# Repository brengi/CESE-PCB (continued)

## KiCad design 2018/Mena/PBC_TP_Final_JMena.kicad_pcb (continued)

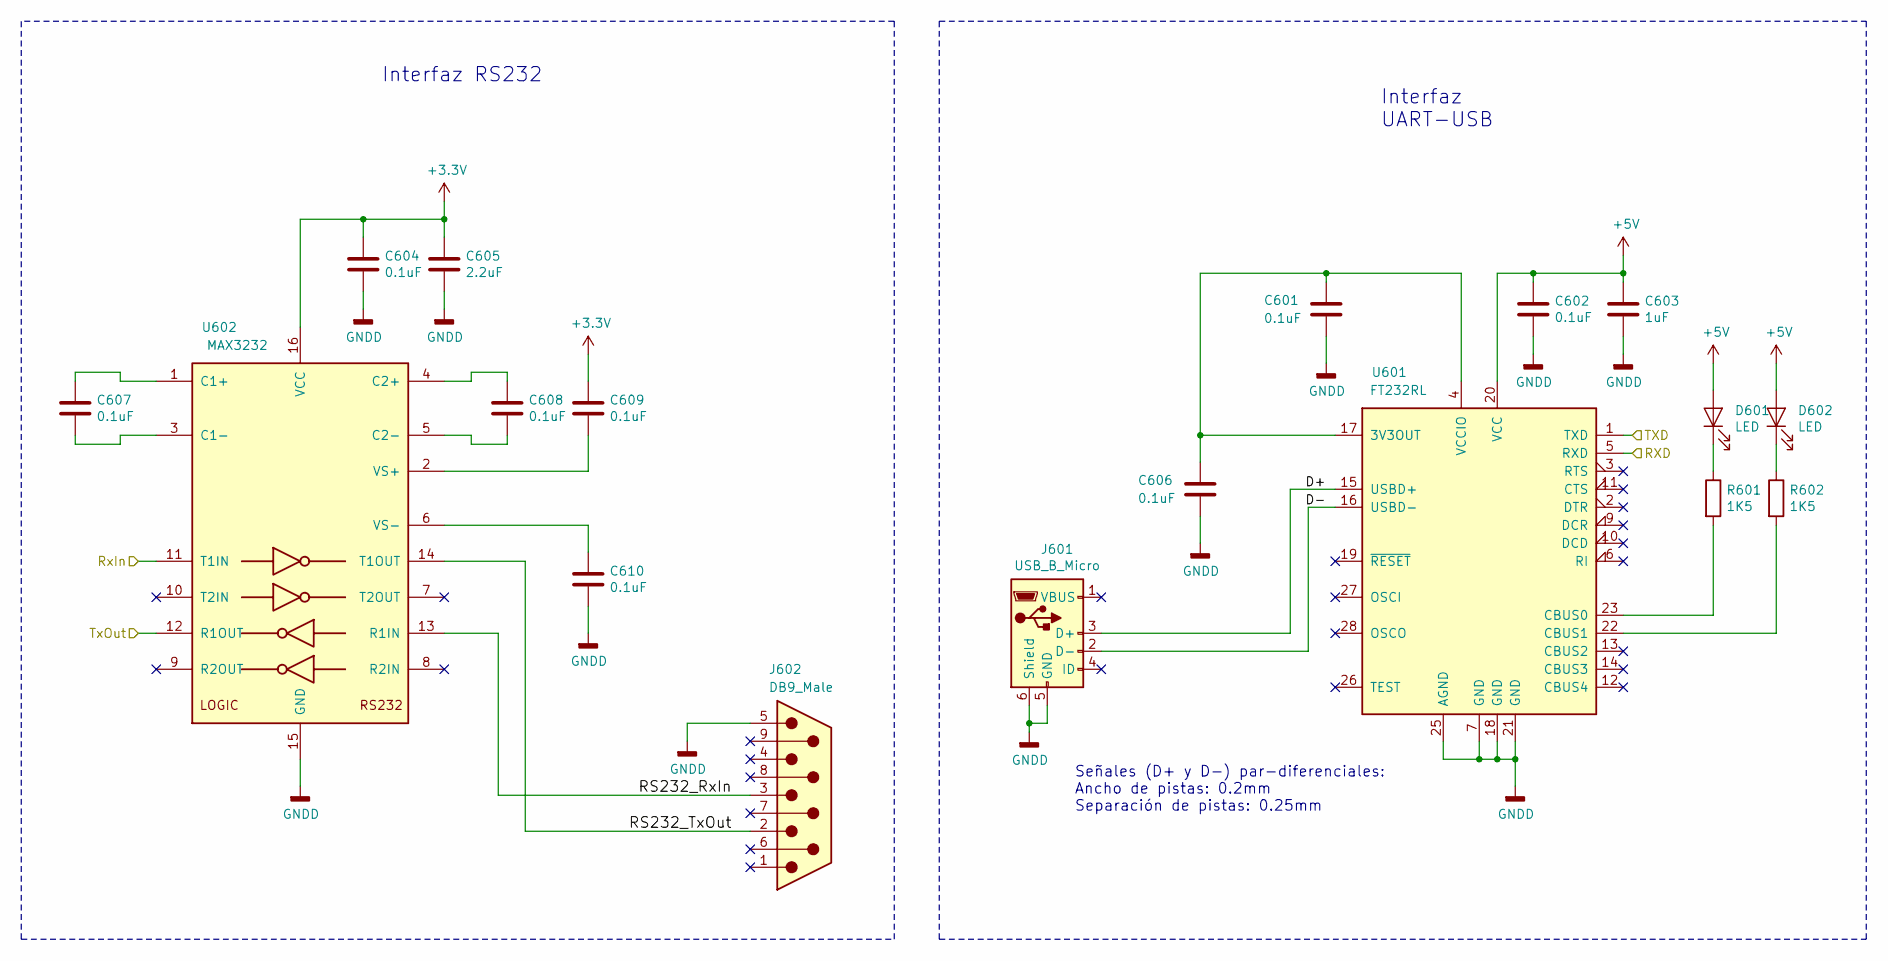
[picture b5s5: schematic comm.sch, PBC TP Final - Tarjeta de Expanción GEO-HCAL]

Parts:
C601, C602, C604, C606, C607, C608, C609, C610: 0.1uF; C_0805_2012Metric_Pad1.15x1.40mm_HandSolder
C603: 1uF; C_0805_2012Metric_Pad1.15x1.40mm_HandSolder
C605: 2.2uF; C_1206_3216Metric_Pad1.42x1.75mm_HandSolder
D601, D602: LED; LED_0805_2012Metric_Pad1.15x1.40mm_HandSolder
J601: USB_B_Micro; USB_Micro-B_Molex_47346-0001
J602: DB9_Male; DSUB-9_Male_Horizontal_P2.77x2.84mm_EdgePinOffset4.94mm_Hou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
R601, R602: 1K5; R_0805_2012Metric_Pad1.15x1.40mm_HandSolder
U601: FT232RL; SSOP-28_5.3x10.2mm_P0.65mm
U602: MAX3232; SOIC-16_3.9x9.9mm_P1.27mm

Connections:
+5V: C602.1, C603.1, D601.2 (A), D602.2 (A), U601.20 (VCC); also elsewhere on the board
/Comunicación/D+: J601.3 (D+), U601.15 (USBD+)
/Comunicación/D-: J601.2 (D-), U601.16 (USBD-)
/Comunicación/RS232_RxIn: J602.3, U602.13 (R1IN)
/Comunicación/RS232_TxOut: J602.2, U602.14 (T1OUT)
/Comunicación/RXD: U601.5 (RXD); also elsewhere on the board
/Comunicación/RxIn: U602.11 (T1IN); also elsewhere on the board
/Comunicación/TXD: U601.1 (TXD); also elsewhere on the board
/Comunicación/TxOut: U602.12 (R1OUT); also elsewhere on the board
GNDD: C601.2, C602.2, C603.2, C604.2, C605.2, C606.2, C610.2, J601.5 (GND), J601.6 (Shield), J602.5, U601.7 (GND), U601.18 (GND), U601.21 (GND), U601.25 (AGND), U602.15 (GND); also elsewhere on the board
unnamed: C601.1, C606.1, U601.4 (VCCIO), U601.17 (3V3OUT)
unnamed: C607.1, U602.1 (C1+)
unnamed: C607.2, U602.3 (C1-)
unnamed: C608.1, U602.4 (C2+)
unnamed: C608.2, U602.5 (C2-)
unnamed: C609.2, U602.2 (VS+)
unnamed: C610.1, U602.6 (VS-)
unnamed: D601.1 (K), R601.1
unnamed: D602.1 (K), R602.1
unnamed: R601.2, U601.23 (CBUS0)
unnamed: R602.2, U601.22 (CBUS1)

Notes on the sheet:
Interfaz RS232
Interfaz UART-USB
Señales (D+ y D-) par-diferenciales: Ancho de pistas: 0.2mm Separación de pistas: 0.25mm

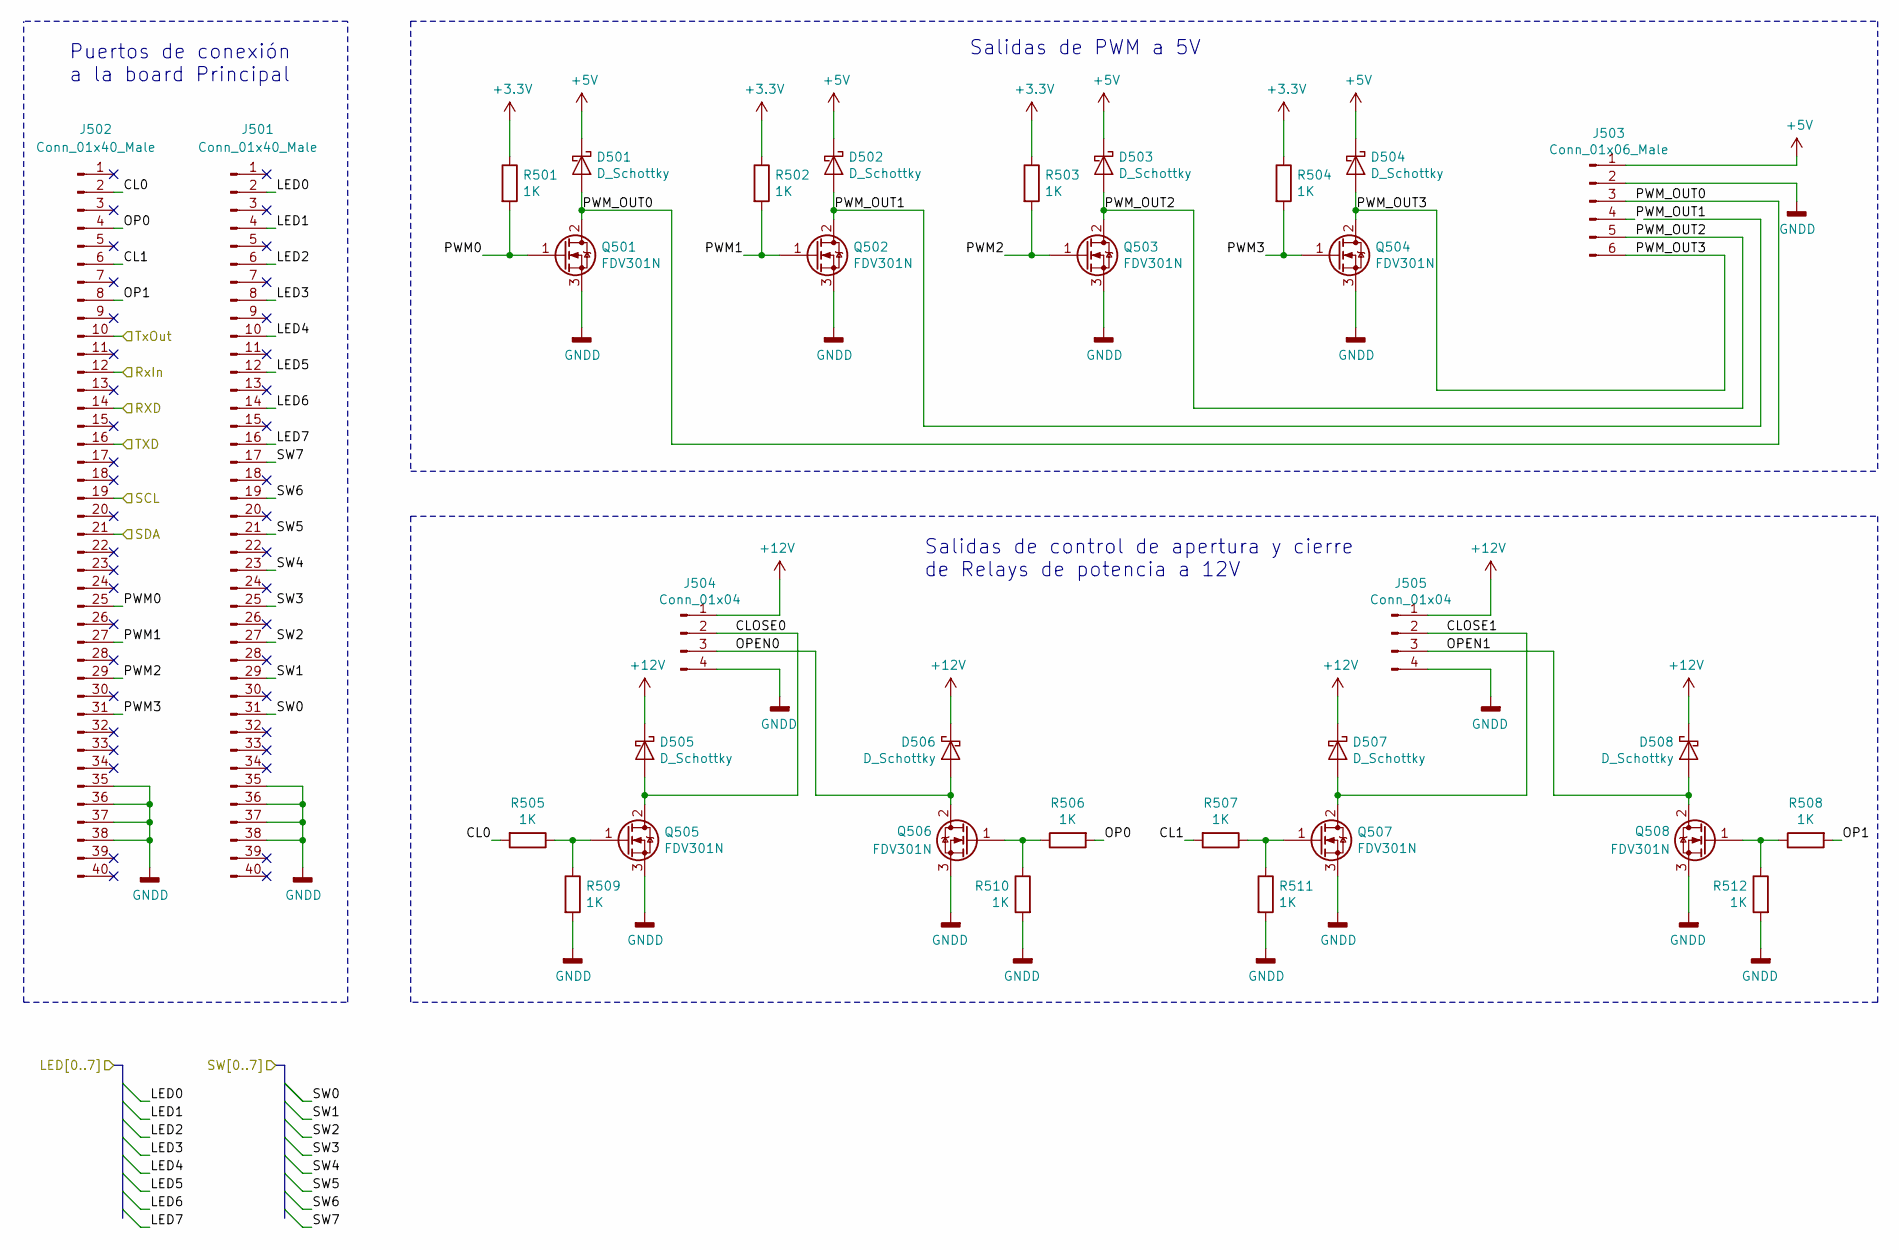
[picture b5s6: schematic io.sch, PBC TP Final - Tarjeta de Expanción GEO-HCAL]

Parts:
D501, D502, D503, D504, D505, D506, D507, D508: D_Schottky; D_0805_2012Metric_Pad1.15x1.40mm_HandSolder
J501, J502: Conn_01x40_Male; PinHeader_2x20_P1.00mm_Vertical
J503: Conn_01x06_Male; PinHeader_1x06_P1.27mm_Vertical
J504, J505: Conn_01x04; PinHeader_1x04_P1.27mm_Vertical
Q501, Q502, Q503, Q504, Q505, Q506, Q507, Q508: FDV301N; SOT-23
R501, R502, R503, R504, R505, R506, R507, R508, R509, R510, R511, R512: 1K; R_0805_2012Metric_Pad1.15x1.40mm_HandSolder

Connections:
+5V: D501.1 (K), D502.1 (K), D503.1 (K), D504.1 (K), J503.1; also elsewhere on the board
+12V: D505.1 (K), D506.1 (K), D507.1 (K), D508.1 (K), J504.1, J505.1; also elsewhere on the board
/Comunicación/RXD: J502.14; also elsewhere on the board
/Comunicación/RxIn: J502.12; also elsewhere on the board
/Comunicación/TXD: J502.16; also elsewhere on the board
/Comunicación/TxOut: J502.10; also elsewhere on the board
/Conversión Analogo-Digital/SCL: J502.19; also elsewhere on the board
/Conversión Analogo-Digital/SDA: J502.21; also elsewhere on the board
/Interfaz de Usuario/LED0: J501.2; also elsewhere on the board
/Interfaz de Usuario/LED1: J501.4; also elsewhere on the board
/Interfaz de Usuario/LED2: J501.6; also elsewhere on the board
/Interfaz de Usuario/LED3: J501.8; also elsewhere on the board
/Interfaz de Usuario/LED4: J501.10; also elsewhere on the board
/Interfaz de Usuario/LED5: J501.12; also elsewhere on the board
/Interfaz de Usuario/LED6: J501.14; also elsewhere on the board
/Interfaz de Usuario/LED7: J501.16; also elsewhere on the board
/Interfaz de Usuario/SW0: J501.31; also elsewhere on the board
/Interfaz de Usuario/SW1: J501.29; also elsewhere on the board
/Interfaz de Usuario/SW2: J501.27; also elsewhere on the board
/Interfaz de Usuario/SW3: J501.25; also elsewhere on the board
/Interfaz de Usuario/SW4: J501.23; also elsewhere on the board
/Interfaz de Usuario/SW5: J501.21; also elsewhere on the board
/Interfaz de Usuario/SW6: J501.19; also elsewhere on the board
/Interfaz de Usuario/SW7: J501.17; also elsewhere on the board
/Puertos de Entrada y Salida/CL0: J502.2, R505.2
/Puertos de Entrada y Salida/CL1: J502.6, R507.2
/Puertos de Entrada y Salida/CLOSE0: D505.2 (A), J504.2, Q505.2 (D)
/Puertos de Entrada y Salida/CLOSE1: D507.2 (A), J505.2, Q507.2 (D)
/Puertos de Entrada y Salida/OP0: J502.4, R506.2
/Puertos de Entrada y Salida/OP1: J502.8, R508.2
/Puertos de Entrada y Salida/OPEN0: D506.2 (A), J504.3, Q506.2 (D)
/Puertos de Entrada y Salida/OPEN1: D508.2 (A), J505.3, Q508.2 (D)
/Puertos de Entrada y Salida/PWM0: J502.25, Q501.1 (G), R501.2
/Puertos de Entrada y Salida/PWM1: J502.27, Q502.1 (G), R502.2
/Puertos de Entrada y Salida/PWM2: J502.29, Q503.1 (G), R503.2
/Puertos de Entrada y Salida/PWM3: J502.31, Q504.1 (G), R504.2
/Puertos de Entrada y Salida/PWM_OUT0: D501.2 (A), J503.3, Q501.2 (D)
/Puertos de Entrada y Salida/PWM_OUT1: D502.2 (A), J503.4, Q502.2 (D)
/Puertos de Entrada y Salida/PWM_OUT2: D503.2 (A), J503.5, Q503.2 (D)
/Puertos de Entrada y Salida/PWM_OUT3: D504.2 (A), J503.6, Q504.2 (D)
GNDD: J501.35, J501.36, J501.37, J501.38, J502.35, J502.36, J502.37, J502.38, J503.2, J504.4, J505.4, Q501.3 (S), Q502.3 (S), Q503.3 (S), Q504.3 (S), Q505.3 (S), Q506.3 (S), Q507.3 (S), Q508.3 (S), R509.2, R510.2, R511.2, R512.2; also elsewhere on the board
unnamed: Q505.1 (G), R505.1, R509.1
unnamed: Q506.1 (G), R506.1, R510.1
unnamed: Q507.1 (G), R507.1, R511.1
unnamed: Q508.1 (G), R508.1, R512.1

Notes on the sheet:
Puertos de conexión a la board Principal
Salidas de PWM a 5V
Salidas de control de apertura y cierre de Relays de potencia a 12V

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
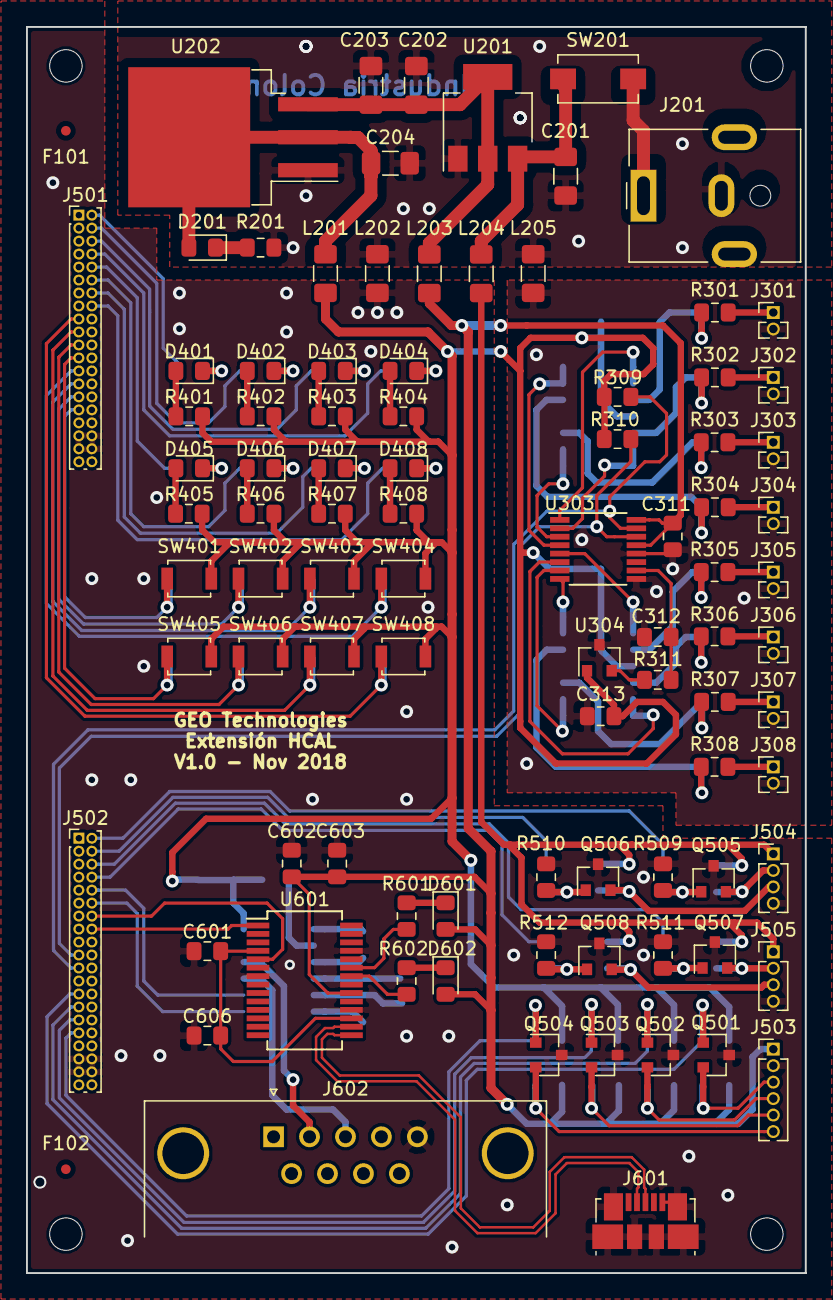
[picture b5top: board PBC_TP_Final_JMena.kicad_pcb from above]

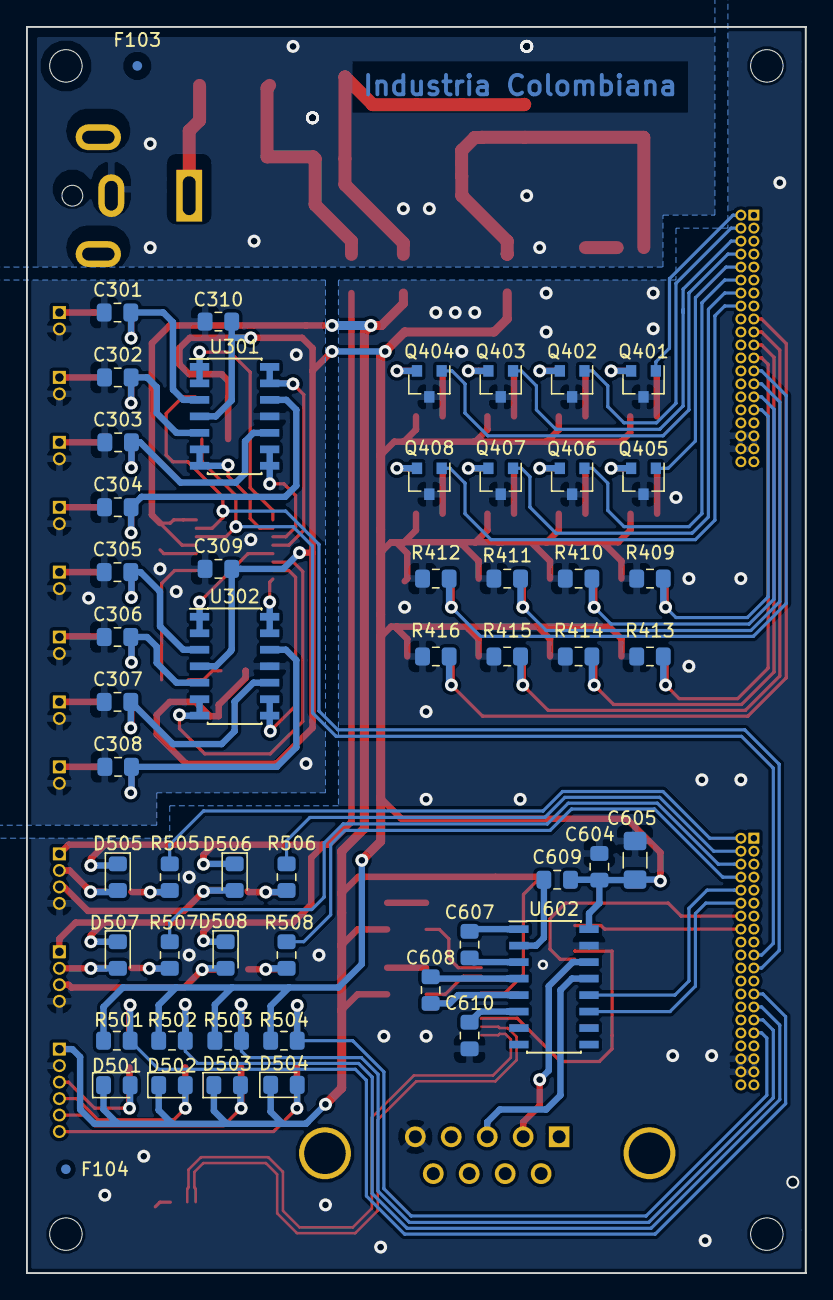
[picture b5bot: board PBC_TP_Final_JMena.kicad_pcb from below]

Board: 2 copper layers, 60.0 x 96.0 mm, 150 parts (53 on the bottom side), 110 nets.

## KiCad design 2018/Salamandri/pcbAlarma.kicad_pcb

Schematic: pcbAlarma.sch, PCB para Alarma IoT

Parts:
F1, F2, F3: Fiducial; Fiducial_1mm_Dia_2mm_Outer
H1, H2, H3: MountingHole; MountingHole_2.2mm_M2
J101: PinMachoSensor; PinHeader_1x02_P2.54mm_Vertical
J102: TiraDePinesHembra; PinSocket_1x06_P2.54mm_Vertical
R3: 180; R_Axial_DIN0207_L6.3mm_D2.5mm_P10.16mm_Horizontal
U2: ESP32-WROOM; ESP32-WROOM-32

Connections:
+3V3: J102.2, R3.2, U2.2; also elsewhere on the board
/EN: J102.3, R3.1, U2.3
/GPIO0: J102.6, U2.25
/Salidas/LedControl: U2.30; also elsewhere on the board
/Salidas/LedStatus: U2.31; also elsewhere on the board
/Salidas/RelayIN: U2.32; also elsewhere on the board
GND: J101.1, J102.1, U2.1; also elsewhere on the board
unnamed: J101.2, U2.37
unnamed: J102.4, U2.34
unnamed: J102.5, U2.35

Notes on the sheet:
Programacion de Microcontrolador

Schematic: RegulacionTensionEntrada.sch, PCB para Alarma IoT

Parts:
C1, C2: 10uF; CP_Radial_D5.0mm_P2.50mm
D1: LED; LED_D3.0mm
J1: USB_B_Mcro
R1: 180; R_Axial_DIN0207_L6.3mm_D2.5mm_P10.16mm_Horizontal
U1: AMS1117; SOT-223-3_TabPin2

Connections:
+3V3: C2.1, R1.1, U1.2 (VO); also elsewhere on the board
+5V: C1.1, J1.1, U1.3 (VI); also elsewhere on the board
GND: C1.2, C2.2, D1.1, J1.5, U1.1 (ADJ); also elsewhere on the board
unnamed: D1.2, R1.2

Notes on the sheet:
Regulacion de Tension de entrada

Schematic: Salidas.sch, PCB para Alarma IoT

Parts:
D2: 1N4003; D_A-405_P10.16mm_Horizontal
D3, D4: LED; LED_D3.0mm
J4: Bornera; TerminalBlock_bornier-2_P5.08mm
K1: Relay; Relay_SPDT_Omron-G5LE-1
Q1: BC337; TO-92_Inline
R2, R4: 180; R_Axial_DIN0207_L6.3mm_D2.5mm_P10.16mm_Horizontal
R5: 330; R_Axial_DIN0207_L6.3mm_D2.5mm_P10.16mm_Horizontal

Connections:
+5V: D2.1 (K), K1.5; also elsewhere on the board
/Salidas/LedControl: R4.2; also elsewhere on the board
/Salidas/LedStatus: R2.2; also elsewhere on the board
/Salidas/RelayIN: R5.1; also elsewhere on the board
GND: D3.1, D4.1, Q1.3 (E); also elsewhere on the board
unnamed: D2.2 (A), K1.1, Q1.1 (C)
unnamed: D3.2, R2.1
unnamed: D4.2, R4.1
unnamed: J4.1, K1.2
unnamed: J4.2, K1.3
unnamed: Q1.2 (B), R5.2

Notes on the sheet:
Salida de potencia
Salidas de control

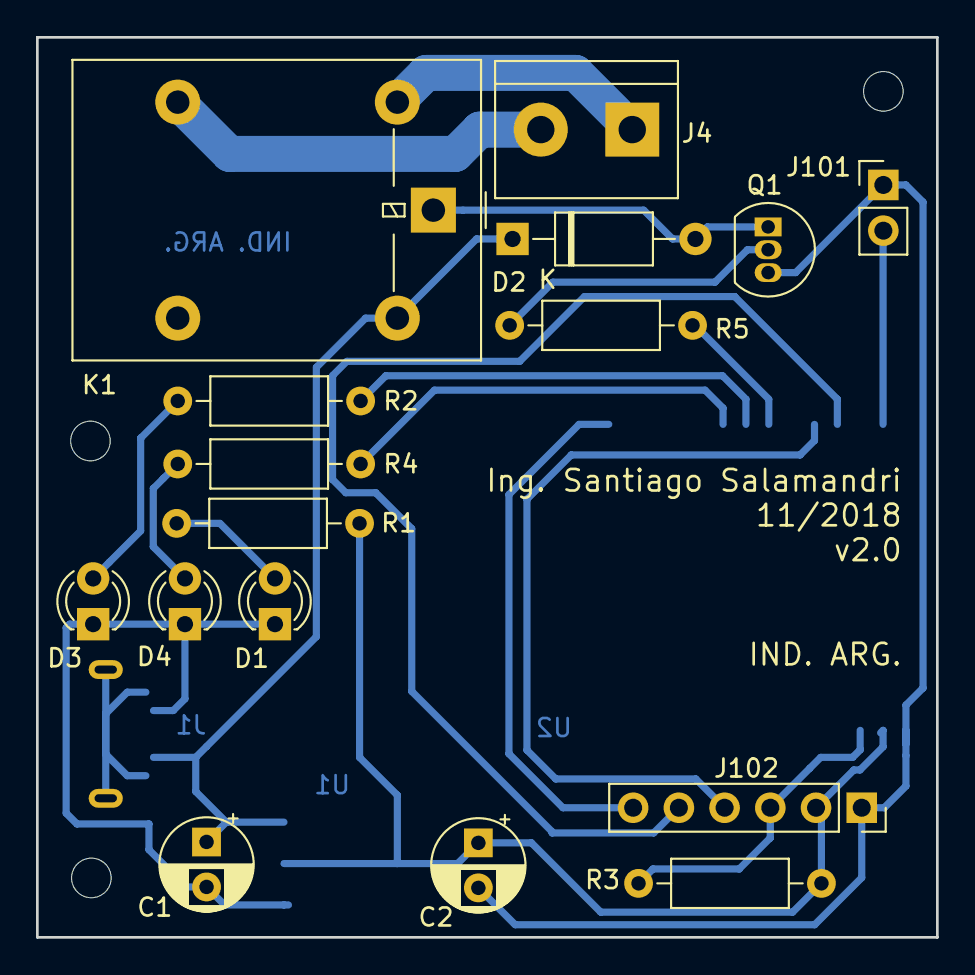
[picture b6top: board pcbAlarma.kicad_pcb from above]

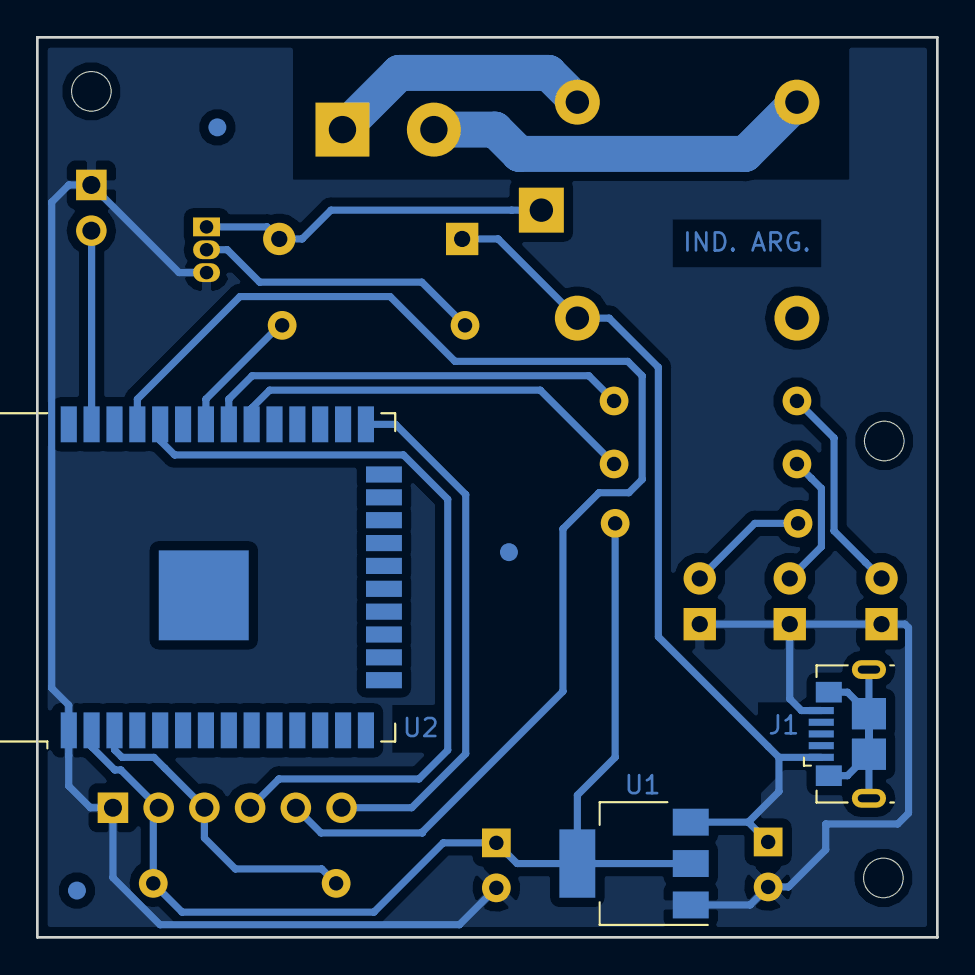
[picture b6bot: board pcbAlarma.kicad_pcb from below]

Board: 2 copper layers, 50.0 x 50.0 mm, 25 parts (6 on the bottom side), 18 nets.

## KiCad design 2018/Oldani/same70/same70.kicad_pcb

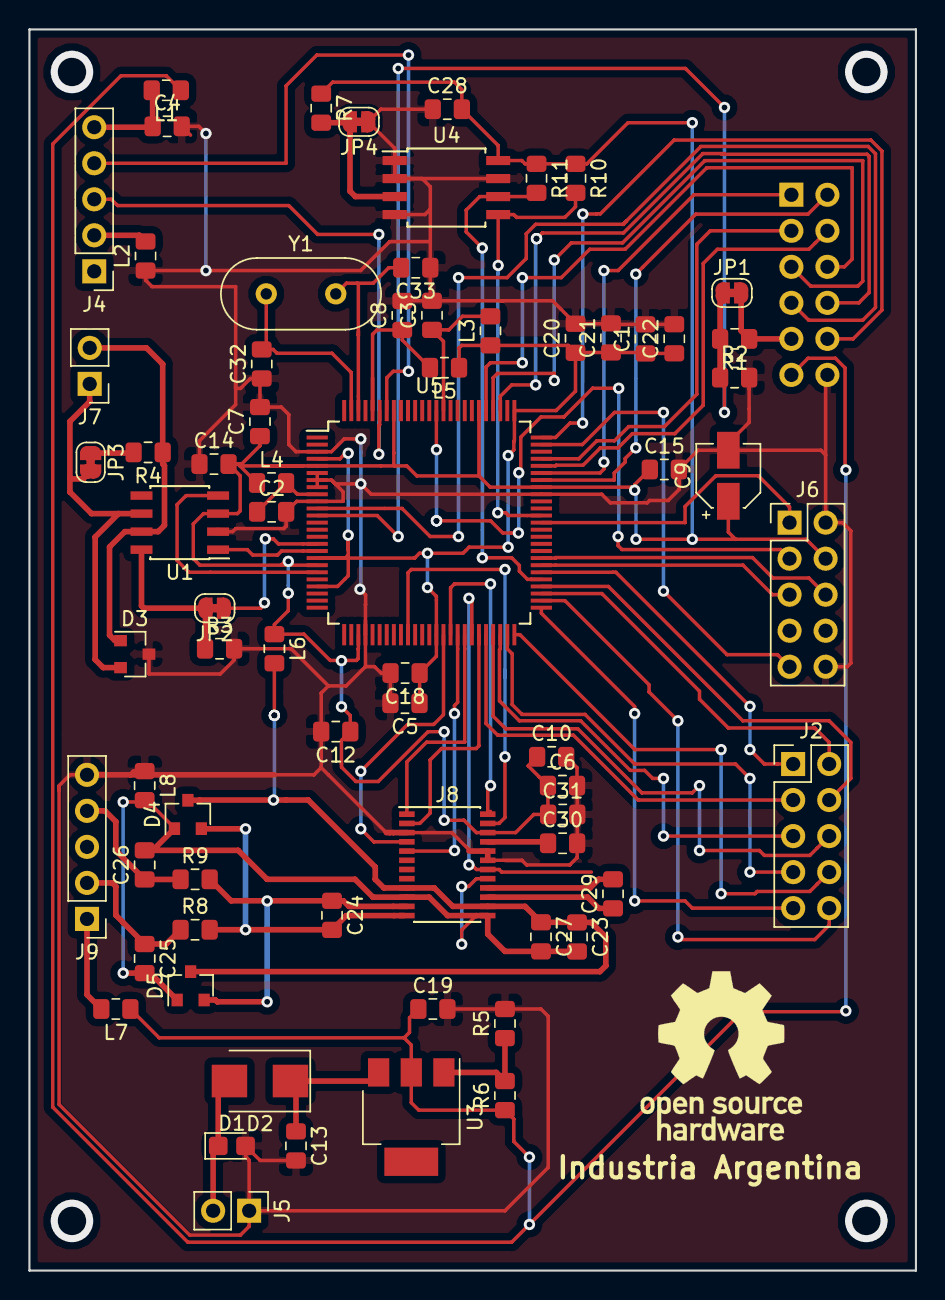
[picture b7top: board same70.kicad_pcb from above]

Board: 2 copper layers, 62.5 x 87.5 mm, 71 parts (1 on the bottom side), 69 nets.

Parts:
C1, C3, C4, C5, C6, C7, C8, C10, C12, C14, C15, C18, C20, C21, C22, C28: 100nF; C_0805_2012Metric_Pad1.15x1.40mm_HandSolder
C2, C13: C; C_0805_2012Metric_Pad1.15x1.40mm_HandSolder
C9: 100uF; CP_Elec_4x5.3
C19, C23, C30, C31: 1uF; C_0805_2012Metric_Pad1.15x1.40mm_HandSolder
C24, C27, C29: 10nF; C_0805_2012Metric_Pad1.15x1.40mm_HandSolder
C25, C26: 10pF; C_0805_2012Metric_Pad1.15x1.40mm_HandSolder
C32, C33: 12pF; C_0805_2012Metric_Pad1.15x1.40mm_HandSolder
D1: D_TVS; D_0805_2012Metric_Castellated
D2: B240; D_SMB
D3: NUP2105L; SOT-23
D4, D5: D_Schottky_x2_Serial_ACK; SOT-23
J2, J6: Conn_02x05_Odd_Even; PinHeader_2x05_P2.54mm_Vertical
J3: Conn_02x06_Odd_Even; PinSocket_2x06_P2.54mm_Vertical
J4: Conn_01x05_Male; PinHeader_1x05_P2.54mm_Vertical
J5, J7: Conn_01x02_Male; PinHeader_1x02_P2.54mm_Vertical
J8: MAX11270; TSSOP-24_4.4x7.8mm_P0.65mm
J9: CeldaCarga; PinHeader_1x05_P2.54mm_Vertical
JP1, JP2, JP3, JP4: SolderJumper_2_Bridged; SolderJumper-2_P1.3mm_Bridged_RoundedPad1.0x1.5mm
L1, L2, L3, L4, L5, L7, L8: L; L_0805_2012Metric_Pad1.15x1.40mm_HandSolder
L6: MMZ1608B601C; L_0805_2012Metric_Pad1.15x1.40mm_HandSolder
R1: 1k8; R_0805_2012Metric_Pad1.15x1.40mm_HandSolder
R2: 3k3; R_0805_2012Metric_Pad1.15x1.40mm_HandSolder
R3, R7, R10, R11: 10k; R_0805_2012Metric_Pad1.15x1.40mm_HandSolder
R4: 120; R_0805_2012Metric_Pad1.15x1.40mm_HandSolder
R5: 1k; R_0805_2012Metric_Pad1.15x1.40mm_HandSolder
R6: 330; R_0805_2012Metric_Pad1.15x1.40mm_HandSolder
R8, R9: 100; R_0805_2012Metric_Pad1.15x1.40mm_HandSolder
U1: SN65HVD230; SOIC-8_3.9x4.9mm_P1.27mm
U3: LM317_3PinPackage; SOT-223
U4: 24LC1025; SOIJ-8_5.3x5.3mm_P1.27mm
U5: ATSAME70N21A-AN; LQFP-100_14x14mm_P0.5mm
Y1: Crystal; Crystal_HC18-U_Vertical

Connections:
35: J8.23, U5.35
40: J8.4, U5.40
41: J8.24, U5.41
42: J8.5, U5.42
43: J8.1, U5.43
44: J8.18, U5.44
45: J8.2, U5.45
46: J2.3, U5.46
47: J2.6, U5.47
48: J2.5, U5.48
49: J2.7, U5.49
50: J2.8, U5.50
51: J2.9, U5.51
52: J2.10, U5.52
53: J2.2, U5.53
54: J2.4, U5.54
55: R11.2, U4.6, U5.55
56: J2.1, U5.56
57: J6.5, U5.57
58: J6.6, U5.58
63: J6.1, U5.63
64: R10.2, U4.5, U5.64
69: J3.2, U5.69
70: J3.1, U5.70
71: J3.4, U5.71
72: J3.3, U5.72
74: J6.9, U5.74
75: J3.10, U5.75
78: J3.8, U5.78
79: J3.5, U5.79
80: J3.6, U5.80
87: J6.3, U5.87
94: J4.4, U5.94
95: J4.3, U5.95
96: C8.1, L5.2, U5.96
98: C33.2, U5.98, Y1.2
99: C32.2, U5.99, Y1.1
+3.3VADC: C23.1, C27.1, D4.3, D5.3, J8.9, J8.14, L6.2
+3V3: C6.1, C7.1, C9.1, C10.1, C12.1, C14.2, C15.1, C28.2, C31.1, J6.4, J8.22, L4.1, L6.1, R7.1, R10.1, R11.1, U1.3, U4.8, U5.5, U5.19, U5.28, U5.68, U5.81, U5.93
+5V: C19.1, J3.11, L1.1, L7.1, R6.1, U3.2
/ANN: C24.1, D5.2, J8.11, R9.2
/ANP: C24.2, D4.2, J8.12, R8.2
CAN_CONF: JP2.1, U5.16
CAN_RX0: U1.4, U5.20
CAN_TX0: U1.1, U5.17
GND: C1.2, C2.2, C3.2, C4.2, C5.2, C6.2, C7.2, C8.2, C9.2, C10.2, C12.2, C13.2, C14.1, C15.2, C18.2, C19.2, C20.2, C21.2, C22.2, C28.1, C30.2, C31.2, C32.1, C33.1, D1.2, D3.3, J3.12, J5.1, J6.2, J6.10, J8.3, J8.19, J8.20, J9.5, JP4.1, L2.1, L8.1, R2.2, R3.2, R5.2, U1.2, U4.1, U4.2, U4.4, U4.7, U5.3, U5.6, U5.7, U5.8, U5.10, U5.29, U5.67
GNDA: C23.2, C25.2, C26.2, C27.2, D4.1, D5.1, J8.10, J8.13, J8.17, L8.2
unnamed: C4.1, J4.5, L1.2
unnamed: C13.1, D2.1, U3.3
unnamed: C25.1, J9.2, R8.1
unnamed: C26.1, J9.4, R9.1
unnamed: C29.1, J8.15
unnamed: C29.2, J8.16
unnamed: C30.1, J8.21
unnamed: D1.1, D2.2, J5.2
unnamed: D3.1, J7.2, R4.1, U1.7
unnamed: D3.2, J7.1, JP3.2, U1.6
unnamed: J3.9, JP1.2, R1.1
unnamed: J4.2, L2.2
unnamed: J9.1, L7.2
unnamed: JP2.2, R3.1, U1.8
unnamed: JP3.1, R4.2
unnamed: JP4.2, R7.2, U4.3
unnamed: R5.1, R6.2, U3.1
RXD0: JP1.1, R1.2, R2.1, U5.12
TXD0: J3.7, U5.11
VDDOUT: C1.1, C5.1, C18.1, C20.1, C21.1, C22.1, L3.1, L5.1, U5.4, U5.18, U5.22, U5.39, U5.76
VDDPLL: C3.1, L3.2, U5.86
VREFP: C2.1, L4.2, U5.9

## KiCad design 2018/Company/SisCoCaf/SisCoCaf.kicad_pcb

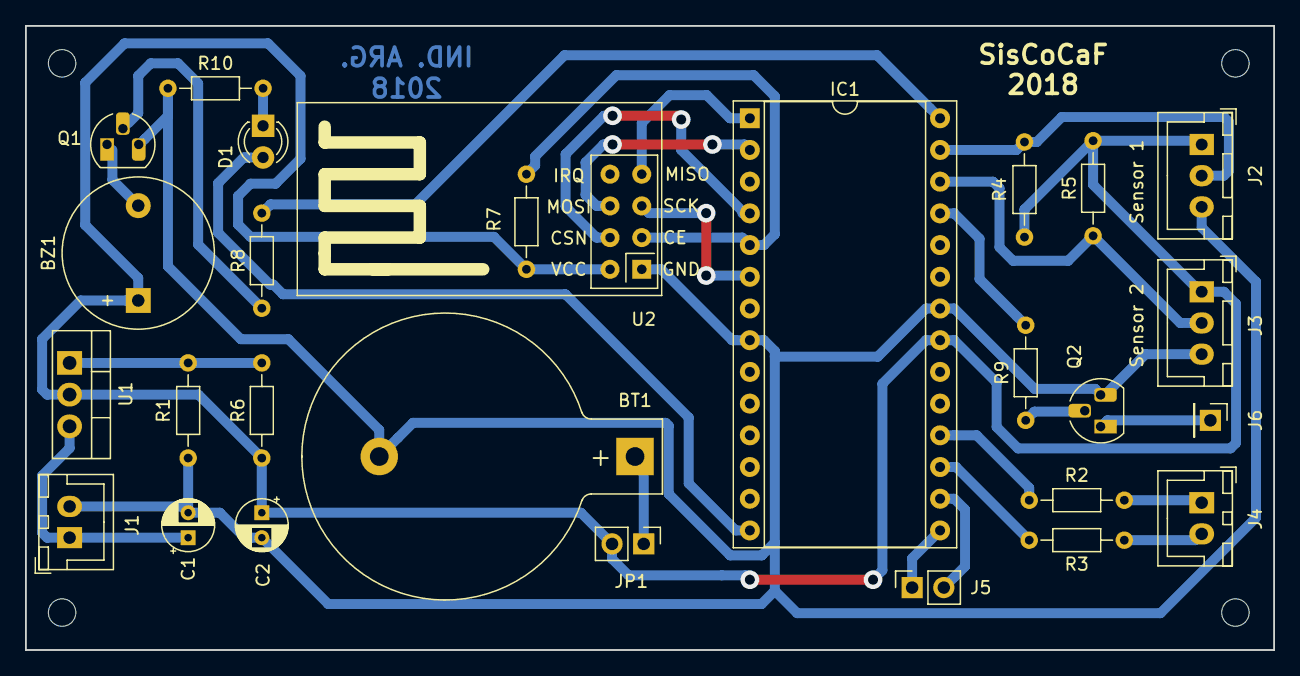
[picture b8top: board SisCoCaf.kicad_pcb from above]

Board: 2 copper layers, 100.0 x 50.0 mm, 31 parts (0 on the bottom side), 26 nets.

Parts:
BT1: Battery_Cell; BatteryHolder_Keystone_103_1x20mm
BZ1: Buzzer; Buzzer_12x9.5RM7.6
C1: 100uf; CP_Radial_D4.0mm_P2.00mm
C2: 220uf; CP_Radial_D4.0mm_P2.00mm
D1: LED; LED_D3.0mm
IC1: LPC111X_102; DIP-28_W15.24mm_Socket
J1: Entrada; JST_XH_B02B-XH-A_1x02_P2.50mm_Vertical
J2, J3: Conn_01x03_Male; JST_XH_B03B-XH-A_1x03_P2.50mm_Vertical
J4: Conn_01x02_Male; JST_XH_B02B-XH-A_1x02_P2.50mm_Vertical
J5: Conn_01x02_Female; PinSocket_1x02_P2.54mm_Vertical
J6: Conn_01x01_Male; PinHeader_1x01_P2.54mm_Vertical
JP1: Jumper; PinHeader_1x02_P2.54mm_Vertical
MH1, MH2, MH3, MH4: MountingHole; MountingHole_2.2mm_M2
Q1, Q2: BC547; TO-92_HandSolder
R1, R6: 1k; R_Axial_DIN0204_L3.6mm_D1.6mm_P7.62mm_Horizontal
R2, R3, R8, R9, R10: 220; R_Axial_DIN0204_L3.6mm_D1.6mm_P7.62mm_Horizontal
R4, R5: 4k7; R_Axial_DIN0204_L3.6mm_D1.6mm_P7.62mm_Horizontal
R7: 5k6; R_Axial_DIN0204_L3.6mm_D1.6mm_P7.62mm_Horizontal
U1: LM317_TO39; TO-220-3_Vertical
U2: NRF24L01_Breakout; nRF24L01_Breakout_antena

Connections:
+12V: C1.1, J1.1, U1.3
/BUZZER: IC1.28, R8.2
/EntradaD1: IC1.18, R2.2
/EntradaD2: IC1.17, R3.2
/LED: D1.2, IC1.14
/RX: IC1.15, J5.1
/SalidaD1: IC1.25, R9.2
/Sensor1: IC1.27, J2.2, R4.1
/Sensor2: IC1.26, J3.2, R5.1
/TX: IC1.16, J5.2
GND: BT1.2, C1.2, C2.2, IC1.8, IC1.22, J1.2, J2.3, J3.3, Q1.3, Q2.3, R1.2, R10.2, U2.1
unnamed: BT1.1, JP1.1
unnamed: BZ1.2, Q1.1
unnamed: D1.1, R10.1
unnamed: IC1.1, U2.7
unnamed: IC1.2, U2.6
unnamed: IC1.4, U2.4
unnamed: IC1.5, R7.2, U2.3
unnamed: IC1.6, U2.5
unnamed: J4.1, R2.1
unnamed: J4.2, R3.1
unnamed: J6.1, Q2.1
unnamed: Q1.2, R8.1
unnamed: Q2.2, R9.1
unnamed: R1.1, R6.2, U1.1
VDD: BZ1.1, C2.1, IC1.21, J2.1, J3.1, JP1.2, R4.2, R5.2, R6.1, R7.1, U1.2, U2.2

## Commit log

2016-07-12 Proyecto Aislacion USB - Primer esquematico
2016-07-13 Aislacion USB - Datos componentes en el SCH
2016-07-18 Se agrego una hoja jerarquica para el ADUM4160 - Se completaron los campos de los componentes
2016-07-19 Se asociaron los footprints
2016-07-20 Se agrego el documento con la revision del SCH
2016-07-20 Rev01 – Se incorporaron las observaciones realizadas en la primera revisión del esquemático - doc:
2016-07-20 Datos fabricante
2016-07-21 Primer ruteo - Se eliminaron los agujeros
2016-07-22 Leyendas en el PCB
2016-07-24 Se agregaron cambios sugeridos por el docente - DOC:Sugerencias Docente 20160724
2016-07-25 Logo en el PCB - Datos del PCB
2016-07-25 Se agregaron los cambios sugueridos en el doc Aislacion USB - Revision PCB 20160725
2016-07-26 Detalles en la Serigrafia - Se agrego la licencia
2016-07-26 Se desconectaron los agujeros del GND
2016-07-26 Se actualizo la rev del PCB y se actualizaron los gerber
2016-07-27 Agrego render 3D del AisladorUSB.
2016-07-27 Agrego AislacionUSB al README.md.
2016-07-27 Agrego vista 3D del poncho Celda de carga.
2016-07-27 Agrego vista 3D del Poncho Osciloscopio.
2016-07-27 Actualizo README.md
2016-07-27 Agrego vista 3d del Poncho Simon.
2016-07-27 Actualizo README.md.
2016-07-27 Agrego un script para reparar vistas 3D.
2016-07-27 Agrego 3D Poncho Amplificador. Recorto las otras vistas 3D.
2016-07-27 Agrego 3d del Poncho detector de caídas.
2016-07-27 Actualizo el README.md.
2016-08-03 Agrego proyecto MICR.
2016-08-23 Agrego Poncho ECG y reorganizo README.md.
2016-09-02 Agrego poncho L298 y SAE. Actualizo links a Ponchos en repo oficial.
2016-09-04 Agrego información del proyecto de Leon Vazquez.
2016-09-04 Agrego presentaciones del primer curso de diseño de PCBs para la CESE.
2016-12-20 Agrego vistas 3D de tres trabajos finales ya concluidos.
2016-12-29 Agrego imágenes de los PCBs del curso nro. 2
2016-12-29 Agrego los Ponchos del curso 2 de la CESE.
2016-12-30 Agregados todos los PCBS del curso 2 de 2016.
2016-12-30 Agrego imágenes de los proyectos inconclusos.
2017-08-21 Agrego imagenes de Ponchos CESE 2017
2017-08-21 Agregado parcial de diseños 2017.
2017-08-21 Agregado parcial de diseños 2017. Tanda 2
2017-08-22 Cambios en las imágenes 3D 2017.
2017-08-22 Fin de carga de proyectos 2017.
2017-08-22 Typo
2019-05-17 Agrego archivos del curso DCI CESE 2018.
2019-05-28 Cambio el README.md y los separo por años. También agrego TOC a los archivos.
2019-05-28 Agrego README 2018
2019-05-28 Mejoras README 2018
2019-05-28 Actualizo TOCs.
2019-05-28 Agrego notas para generar TOCs.
2019-05-28 Corrigo detalles en los READMEs
2019-11-25 Agrego segundo curso de 2019
2019-11-25 Agrego curso 2019 primer semestre.
2019-11-25 Set theme jekyll-theme-minimal
2019-11-25 Mejoro encabezado.
2019-11-25 Corrijo encabezado.
2021-03-04 Agrego imágenes DCI 2020A.
2021-03-04 Agrego TOC para el curso 2020A.
2021-03-04 Agrego imágenes del curso 2020B.
2021-03-04 Agrego TOC del curso 2020B.
2021-03-11 Error en el nombre de un proyecto.
